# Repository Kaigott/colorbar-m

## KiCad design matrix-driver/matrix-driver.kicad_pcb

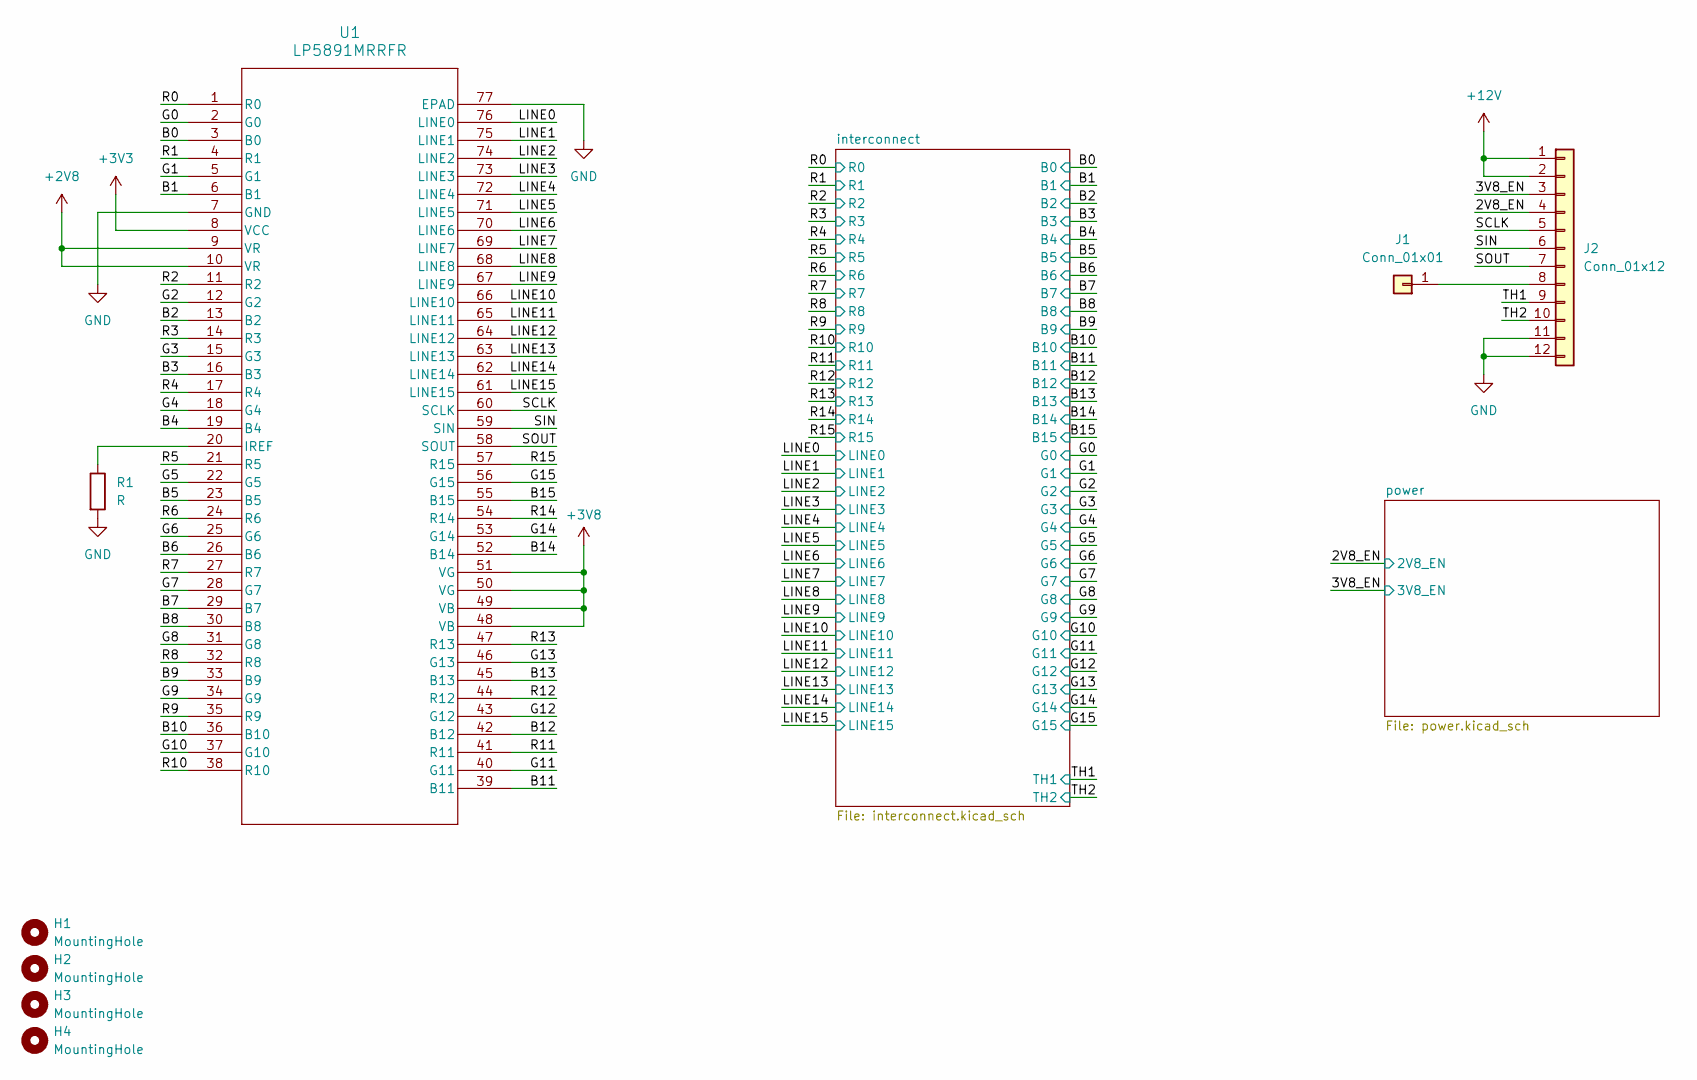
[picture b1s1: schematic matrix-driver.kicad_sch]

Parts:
H1, H2, H3, H4: MountingHole; MountingHole_3.2mm_M3_DIN965
J1: Conn_01x01; PinHeader_1x01_P2.54mm_Vertical
J2: Conn_01x12; JST_XA_B12B-XASK-1-A_1x12_P2.50mm_Vertical
R1: R; R_0603_1608Metric
U1: LP5891MRRFR; VQFN76_RRF_TEX

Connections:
+2V8: U1.9 (VR), U1.10 (VR); also elsewhere on the board
+3V3: U1.8 (VCC); also elsewhere on the board
+3V8: U1.48 (VB), U1.49 (VB), U1.50 (VG), U1.51 (VG); also elsewhere on the board
+12V: J2.1, J2.2; also elsewhere on the board
/2V8_EN: J2.4; also elsewhere on the board
/3V8_EN: J2.3; also elsewhere on the board
/B0: U1.3 (B0); also elsewhere on the board
/B1: U1.6 (B1); also elsewhere on the board
/B2: U1.13 (B2); also elsewhere on the board
/B3: U1.16 (B3); also elsewhere on the board
/B4: U1.19 (B4); also elsewhere on the board
/B5: U1.23 (B5); also elsewhere on the board
/B6: U1.26 (B6); also elsewhere on the board
/B7: U1.29 (B7); also elsewhere on the board
/B8: U1.30 (B8); also elsewhere on the board
/B9: U1.33 (B9); also elsewhere on the board
/B10: U1.36 (B10); also elsewhere on the board
/B11: U1.39 (B11); also elsewhere on the board
/B12: U1.42 (B12); also elsewhere on the board
/B13: U1.45 (B13); also elsewhere on the board
/B14: U1.52 (B14); also elsewhere on the board
/B15: U1.55 (B15); also elsewhere on the board
/G0: U1.2 (G0); also elsewhere on the board
/G1: U1.5 (G1); also elsewhere on the board
/G2: U1.12 (G2); also elsewhere on the board
/G3: U1.15 (G3); also elsewhere on the board
/G4: U1.18 (G4); also elsewhere on the board
/G5: U1.22 (G5); also elsewhere on the board
/G6: U1.25 (G6); also elsewhere on the board
/G7: U1.28 (G7); also elsewhere on the board
/G8: U1.31 (G8); also elsewhere on the board
/G9: U1.34 (G9); also elsewhere on the board
/G10: U1.37 (G10); also elsewhere on the board
/G11: U1.40 (G11); also elsewhere on the board
/G12: U1.43 (G12); also elsewhere on the board
/G13: U1.46 (G13); also elsewhere on the board
/G14: U1.53 (G14); also elsewhere on the board
/G15: U1.56 (G15); also elsewhere on the board
/LINE0: U1.76 (LINE0); also elsewhere on the board
/LINE1: U1.75 (LINE1); also elsewhere on the board
/LINE2: U1.74 (LINE2); also elsewhere on the board
/LINE3: U1.73 (LINE3); also elsewhere on the board
/LINE4: U1.72 (LINE4); also elsewhere on the board
/LINE5: U1.71 (LINE5); also elsewhere on the board
/LINE6: U1.70 (LINE6); also elsewhere on the board
/LINE7: U1.69 (LINE7); also elsewhere on the board
/LINE8: U1.68 (LINE8); also elsewhere on the board
/LINE9: U1.67 (LINE9); also elsewhere on the board
/LINE10: U1.66 (LINE10); also elsewhere on the board
/LINE11: U1.65 (LINE11); also elsewhere on the board
/LINE12: U1.64 (LINE12); also elsewhere on the board
/LINE13: U1.63 (LINE13); also elsewhere on the board
/LINE14: U1.62 (LINE14); also elsewhere on the board
/LINE15: U1.61 (LINE15); also elsewhere on the board
/R0: U1.1 (R0); also elsewhere on the board
/R1: U1.4 (R1); also elsewhere on the board
/R2: U1.11 (R2); also elsewhere on the board
/R3: U1.14 (R3); also elsewhere on the board
/R4: U1.17 (R4); also elsewhere on the board
/R5: U1.21 (R5); also elsewhere on the board
/R6: U1.24 (R6); also elsewhere on the board
/R7: U1.27 (R7); also elsewhere on the board
/R8: U1.32 (R8); also elsewhere on the board
/R9: U1.35 (R9); also elsewhere on the board
/R10: U1.38 (R10); also elsewhere on the board
/R11: U1.41 (R11); also elsewhere on the board
/R12: U1.44 (R12); also elsewhere on the board
/R13: U1.47 (R13); also elsewhere on the board
/R14: U1.54 (R14); also elsewhere on the board
/R15: U1.57 (R15); also elsewhere on the board
/SCLK: J2.5, U1.60 (SCLK)
/SIN: J2.6, U1.59 (SIN)
/SOUT: J2.7, U1.58 (SOUT)
/TH1: J2.9; also elsewhere on the board
/TH2: J2.10; also elsewhere on the board
GND: J2.11, J2.12, R1.2, U1.7 (GND), U1.77 (EPAD); also elsewhere on the board
unnamed: J1.1, J2.8
unnamed: R1.1, U1.20 (IREF)

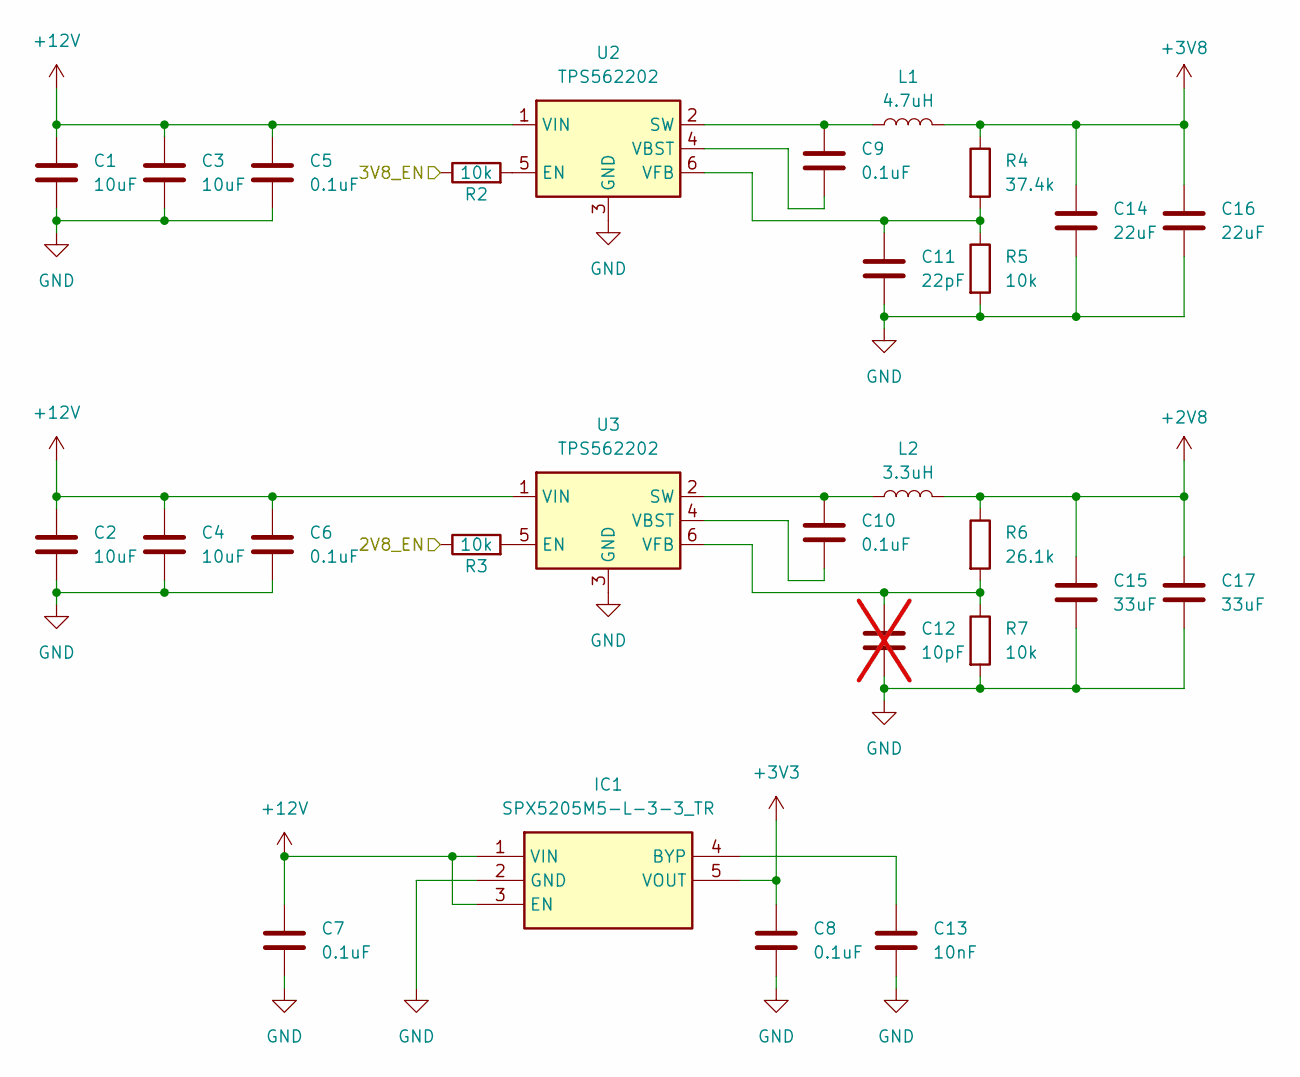
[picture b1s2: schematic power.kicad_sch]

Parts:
C1, C2, C3, C4: 10uF; C_1206_3216Metric
C5, C6, C7, C8, C9, C10: 0.1uF; C_0603_1608Metric
C11: 22pF; C_0603_1608Metric
C12: 10pF; C_0603_1608Metric; not fitted
C13: 10nF; C_0603_1608Metric
C14, C16: 22uF; C_1206_3216Metric
C15, C17: 33uF; C_1206_3216Metric
IC1: SPX5205M5-L-3-3_TR; SOT-23-5; Mouser Part Number 701-SPX5205M5-L-33TR
L1: 4.7uH; IND_PCC-M0530M-LP_PAN
L2: 3.3uH; IND_PCC-M0530M-LP_PAN
R2, R3, R5, R7: 10k; R_0603_1608Metric
R4: 37.4k; R_0603_1608Metric
R6: 26.1k; R_0603_1608Metric
U2, U3: TPS562202; SOT-563

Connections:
+2V8: C15.2, C17.2, L2.2, R6.1; also elsewhere on the board
+3V3: C8.1, IC1.5 (VOUT); also elsewhere on the board
+3V8: C14.2, C16.2, L1.2, R4.1; also elsewhere on the board
+12V: C1.1, C2.1, C3.1, C4.1, C5.1, C6.1, C7.1, IC1.1 (VIN), IC1.3 (EN), U2.1 (VIN), U3.1 (VIN); also elsewhere on the board
/2V8_EN: R3.1; also elsewhere on the board
/3V8_EN: R2.1; also elsewhere on the board
GND: C1.2, C2.2, C3.2, C4.2, C5.2, C6.2, C7.2, C8.2, C11.1, C12.1, C13.2, C14.1, C15.1, C16.1, C17.1, IC1.2 (GND), R5.2, R7.2, U2.3 (GND), U3.3 (GND); also elsewhere on the board
unnamed: C13.1, IC1.4 (BYP)
unnamed: R2.2, U2.5 (EN)
unnamed: C9.1, L1.1, U2.2 (SW)
unnamed: C9.2, U2.4 (VBST)
unnamed: C11.2, R4.2, R5.1, U2.6 (VFB)
unnamed: R3.2, U3.5 (EN)
unnamed: C10.1, L2.1, U3.2 (SW)
unnamed: C10.2, U3.4 (VBST)
unnamed: C12.2, R6.2, R7.1, U3.6 (VFB)

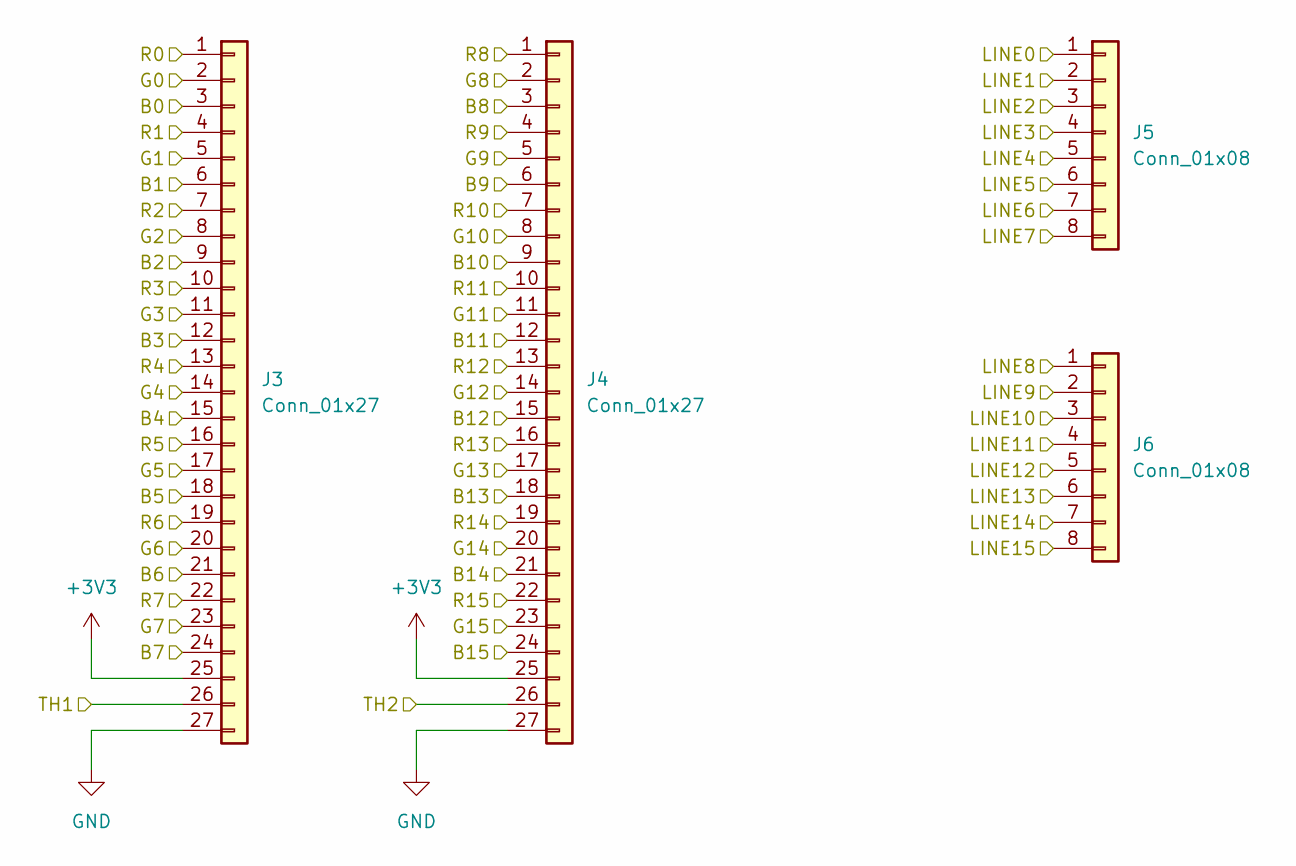
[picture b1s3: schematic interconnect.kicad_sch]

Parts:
J3, J4: Conn_01x27; Hirose_FH26-27S-0.3SHW_2Rows-27Pins-1MP_P0.60mm_Horizontal
J5, J6: Conn_01x08; JST_XA_B08B-XASK-1-A_1x08_P2.50mm_Vertical

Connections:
+3V3: J3.25, J4.25; also elsewhere on the board
/B0: J3.3; also elsewhere on the board
/B1: J3.6; also elsewhere on the board
/B2: J3.9; also elsewhere on the board
/B3: J3.12; also elsewhere on the board
/B4: J3.15; also elsewhere on the board
/B5: J3.18; also elsewhere on the board
/B6: J3.21; also elsewhere on the board
/B7: J3.24; also elsewhere on the board
/B8: J4.3; also elsewhere on the board
/B9: J4.6; also elsewhere on the board
/B10: J4.9; also elsewhere on the board
/B11: J4.12; also elsewhere on the board
/B12: J4.15; also elsewhere on the board
/B13: J4.18; also elsewhere on the board
/B14: J4.21; also elsewhere on the board
/B15: J4.24; also elsewhere on the board
/G0: J3.2; also elsewhere on the board
/G1: J3.5; also elsewhere on the board
/G2: J3.8; also elsewhere on the board
/G3: J3.11; also elsewhere on the board
/G4: J3.14; also elsewhere on the board
/G5: J3.17; also elsewhere on the board
/G6: J3.20; also elsewhere on the board
/G7: J3.23; also elsewhere on the board
/G8: J4.2; also elsewhere on the board
/G9: J4.5; also elsewhere on the board
/G10: J4.8; also elsewhere on the board
/G11: J4.11; also elsewhere on the board
/G12: J4.14; also elsewhere on the board
/G13: J4.17; also elsewhere on the board
/G14: J4.20; also elsewhere on the board
/G15: J4.23; also elsewhere on the board
/LINE0: J5.1; also elsewhere on the board
/LINE1: J5.2; also elsewhere on the board
/LINE2: J5.3; also elsewhere on the board
/LINE3: J5.4; also elsewhere on the board
/LINE4: J5.5; also elsewhere on the board
/LINE5: J5.6; also elsewhere on the board
/LINE6: J5.7; also elsewhere on the board
/LINE7: J5.8; also elsewhere on the board
/LINE8: J6.1; also elsewhere on the board
/LINE9: J6.2; also elsewhere on the board
/LINE10: J6.3; also elsewhere on the board
/LINE11: J6.4; also elsewhere on the board
/LINE12: J6.5; also elsewhere on the board
/LINE13: J6.6; also elsewhere on the board
/LINE14: J6.7; also elsewhere on the board
/LINE15: J6.8; also elsewhere on the board
/R0: J3.1; also elsewhere on the board
/R1: J3.4; also elsewhere on the board
/R2: J3.7; also elsewhere on the board
/R3: J3.10; also elsewhere on the board
/R4: J3.13; also elsewhere on the board
/R5: J3.16; also elsewhere on the board
/R6: J3.19; also elsewhere on the board
/R7: J3.22; also elsewhere on the board
/R8: J4.1; also elsewhere on the board
/R9: J4.4; also elsewhere on the board
/R10: J4.7; also elsewhere on the board
/R11: J4.10; also elsewhere on the board
/R12: J4.13; also elsewhere on the board
/R13: J4.16; also elsewhere on the board
/R14: J4.19; also elsewhere on the board
/R15: J4.22; also elsewhere on the board
/TH1: J3.26; also elsewhere on the board
/TH2: J4.26; also elsewhere on the board
GND: J3.27, J4.27; also elsewhere on the board

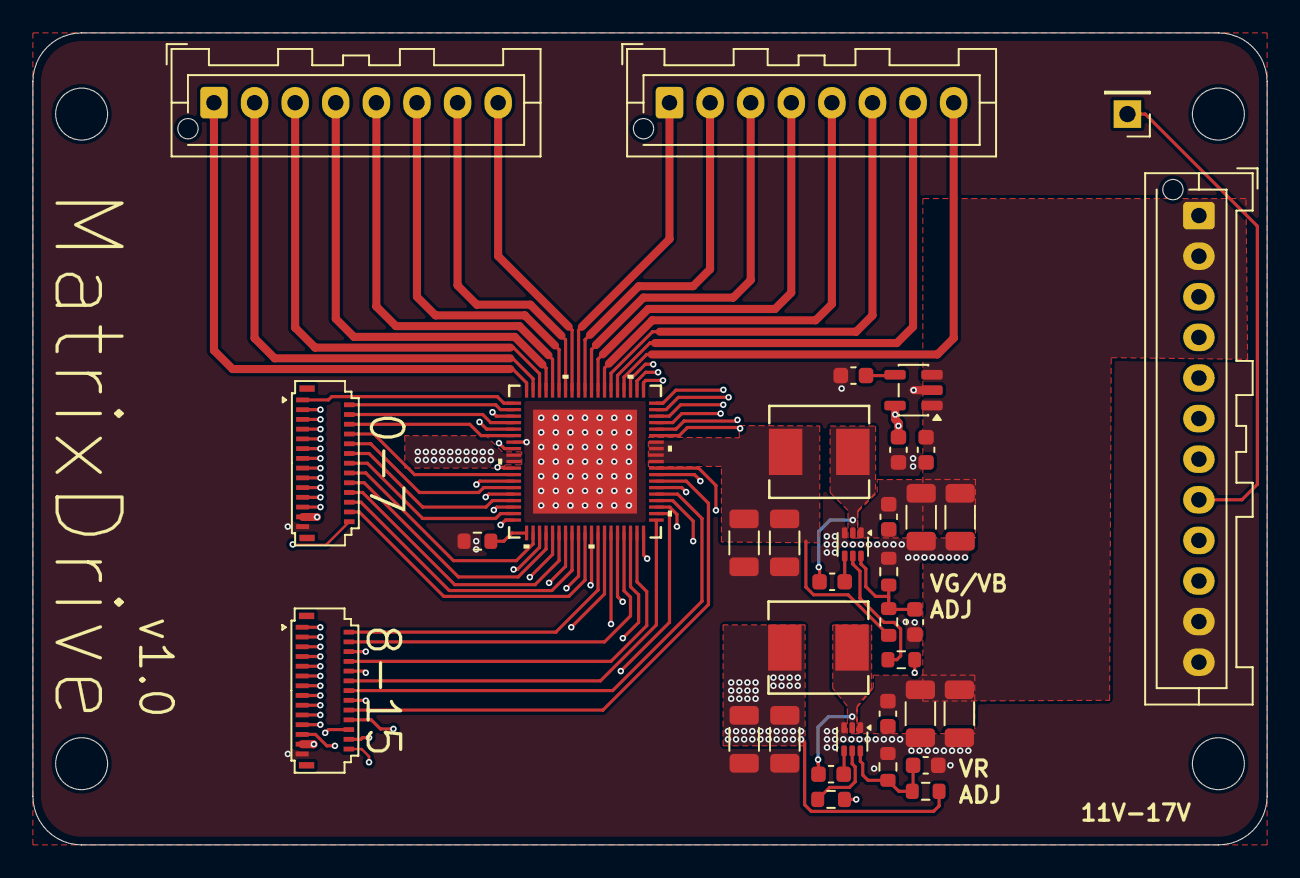
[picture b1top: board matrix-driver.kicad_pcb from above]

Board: 4 copper layers, 76.0 x 50.0 mm, 40 parts (0 on the bottom side), 87 nets.
